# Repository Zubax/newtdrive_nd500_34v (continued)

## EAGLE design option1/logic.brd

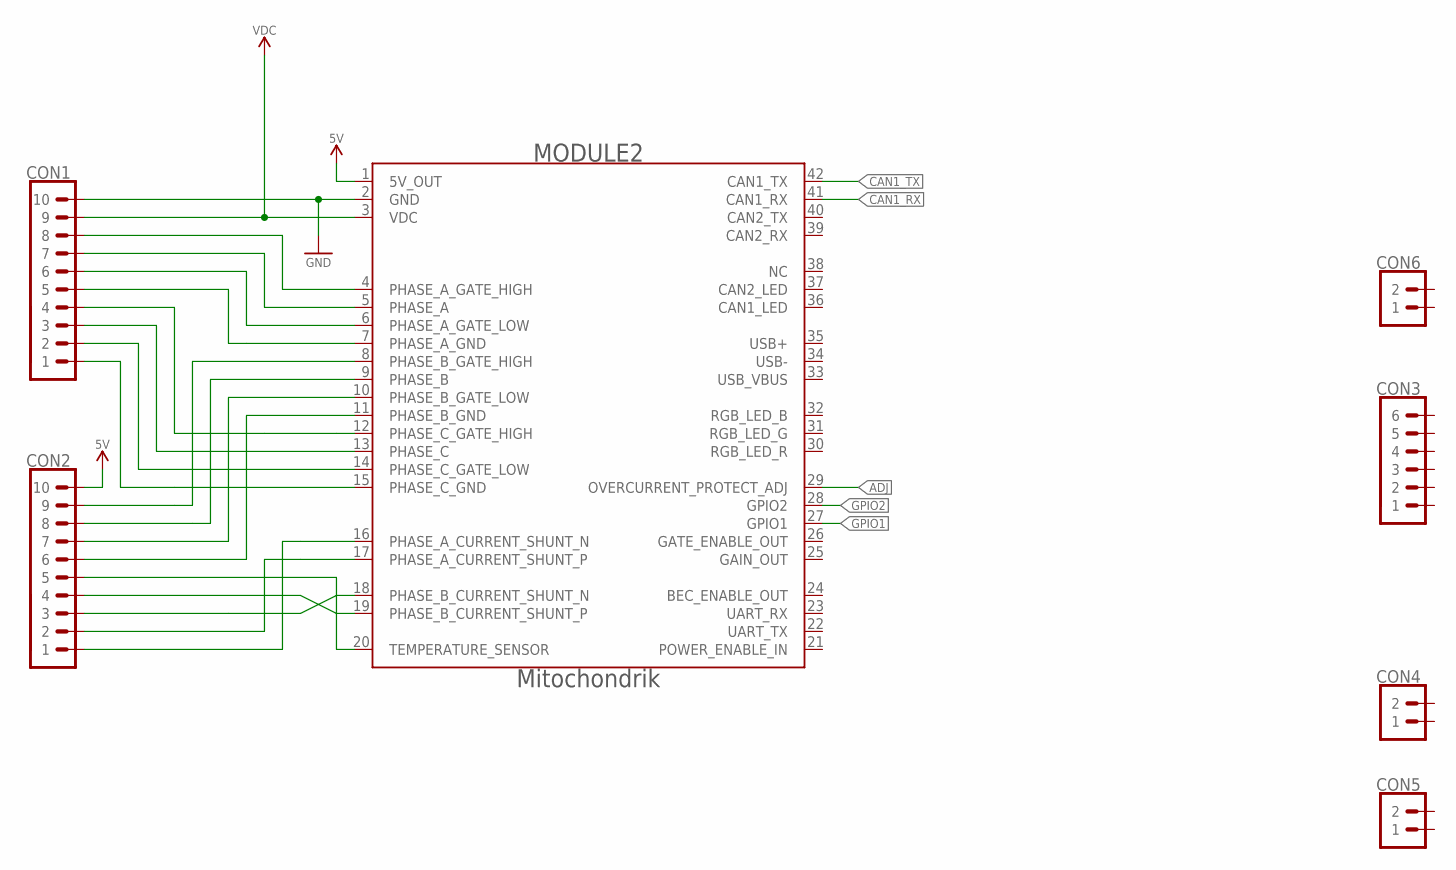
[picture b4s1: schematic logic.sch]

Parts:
CON1, CON2: PINHEAD_1X10-2; 1X10-PTH_2
CON3: PINHEAD_1X06-2; 1X06-PTH-2
CON4, CON5, CON6: PINHEAD_1X02-2; 1X02-PTH-2
MODULE2: MITOHONDRIQUE-TH; MITOHONDRIQUE

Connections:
ADJ: CON3.2, MODULE2.29 (OVERCURRENT_PROTECT_ADJ)
BLUE: CON3.1, MODULE2.32 (RGB_LED_B)
CAN1_LED: CON3.6, MODULE2.36 (CAN1_LED)
CAN1_RX: CON3.4, MODULE2.41 (CAN1_RX)
CAN1_TX: CON3.5, MODULE2.42 (CAN1_TX)
GND: CON1.10, CON5.2, CON6.2, MODULE2.2 (GND)
GPIO1: CON3.3, CON6.1, MODULE2.27 (GPIO1)
GPIO2: MODULE2.28 (GPIO2)
GREEN: CON4.2, MODULE2.31 (RGB_LED_G)
unnamed: CON2.3, MODULE2.18 (PHASE_B_CURRENT_SHUNT_N)
unnamed: CON2.2, MODULE2.17 (PHASE_A_CURRENT_SHUNT_P)
unnamed: CON2.1, MODULE2.16 (PHASE_A_CURRENT_SHUNT_N)
unnamed: CON2.4, MODULE2.19 (PHASE_B_CURRENT_SHUNT_P)
unnamed: CON1.1, MODULE2.15 (PHASE_C_GND)
PHASE_A: CON1.7, MODULE2.5 (PHASE_A)
PHASE_A_GATE_HIGH: CON1.8, MODULE2.4 (PHASE_A_GATE_HIGH)
PHASE_A_GATE_LOW: CON1.6, MODULE2.6 (PHASE_A_GATE_LOW)
PHASE_A_GND: CON1.5, MODULE2.7 (PHASE_A_GND)
PHASE_B: CON1.3, MODULE2.13 (PHASE_C)
PHASE_B_GATE_HIGH: CON1.4, MODULE2.12 (PHASE_C_GATE_HIGH)
PHASE_B_GATE_LOW: CON1.2, MODULE2.14 (PHASE_C_GATE_LOW)
PHASE_C: CON2.8, MODULE2.9 (PHASE_B)
PHASE_C_GATE_HIGH: CON2.9, MODULE2.8 (PHASE_B_GATE_HIGH)
PHASE_C_GATE_LOW: CON2.7, MODULE2.10 (PHASE_B_GATE_LOW)
PHASE_C_GND: CON2.6, MODULE2.11 (PHASE_B_GND)
RED: CON4.1, MODULE2.30 (RGB_LED_R)
TEMPERATURE_SENSOR: CON2.5, MODULE2.20 (TEMPERATURE_SENSOR)
VDC: CON1.9, MODULE2.3 (VDC)
VDD_5V: CON2.10, CON5.1, MODULE2.1 (5V_OUT)

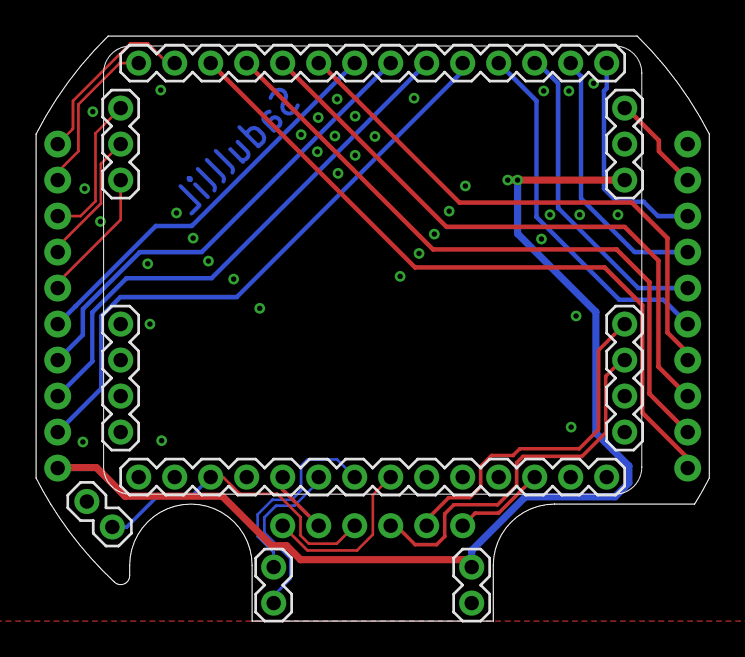
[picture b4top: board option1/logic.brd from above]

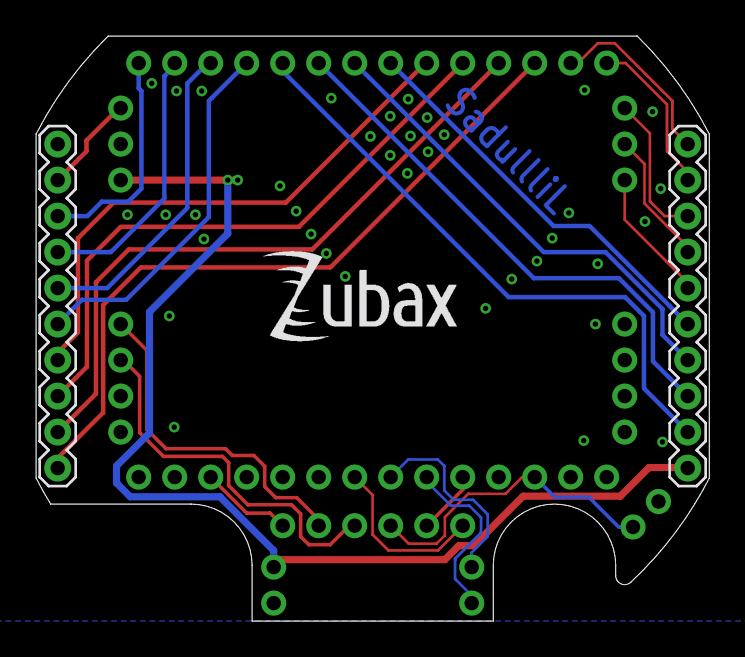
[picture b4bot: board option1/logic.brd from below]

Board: 2 copper layers, 37.4 x 32.5 mm, 8 parts (3 on the bottom side), 28 nets.

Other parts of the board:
U$1: ZUBAX_LOGO_5X10

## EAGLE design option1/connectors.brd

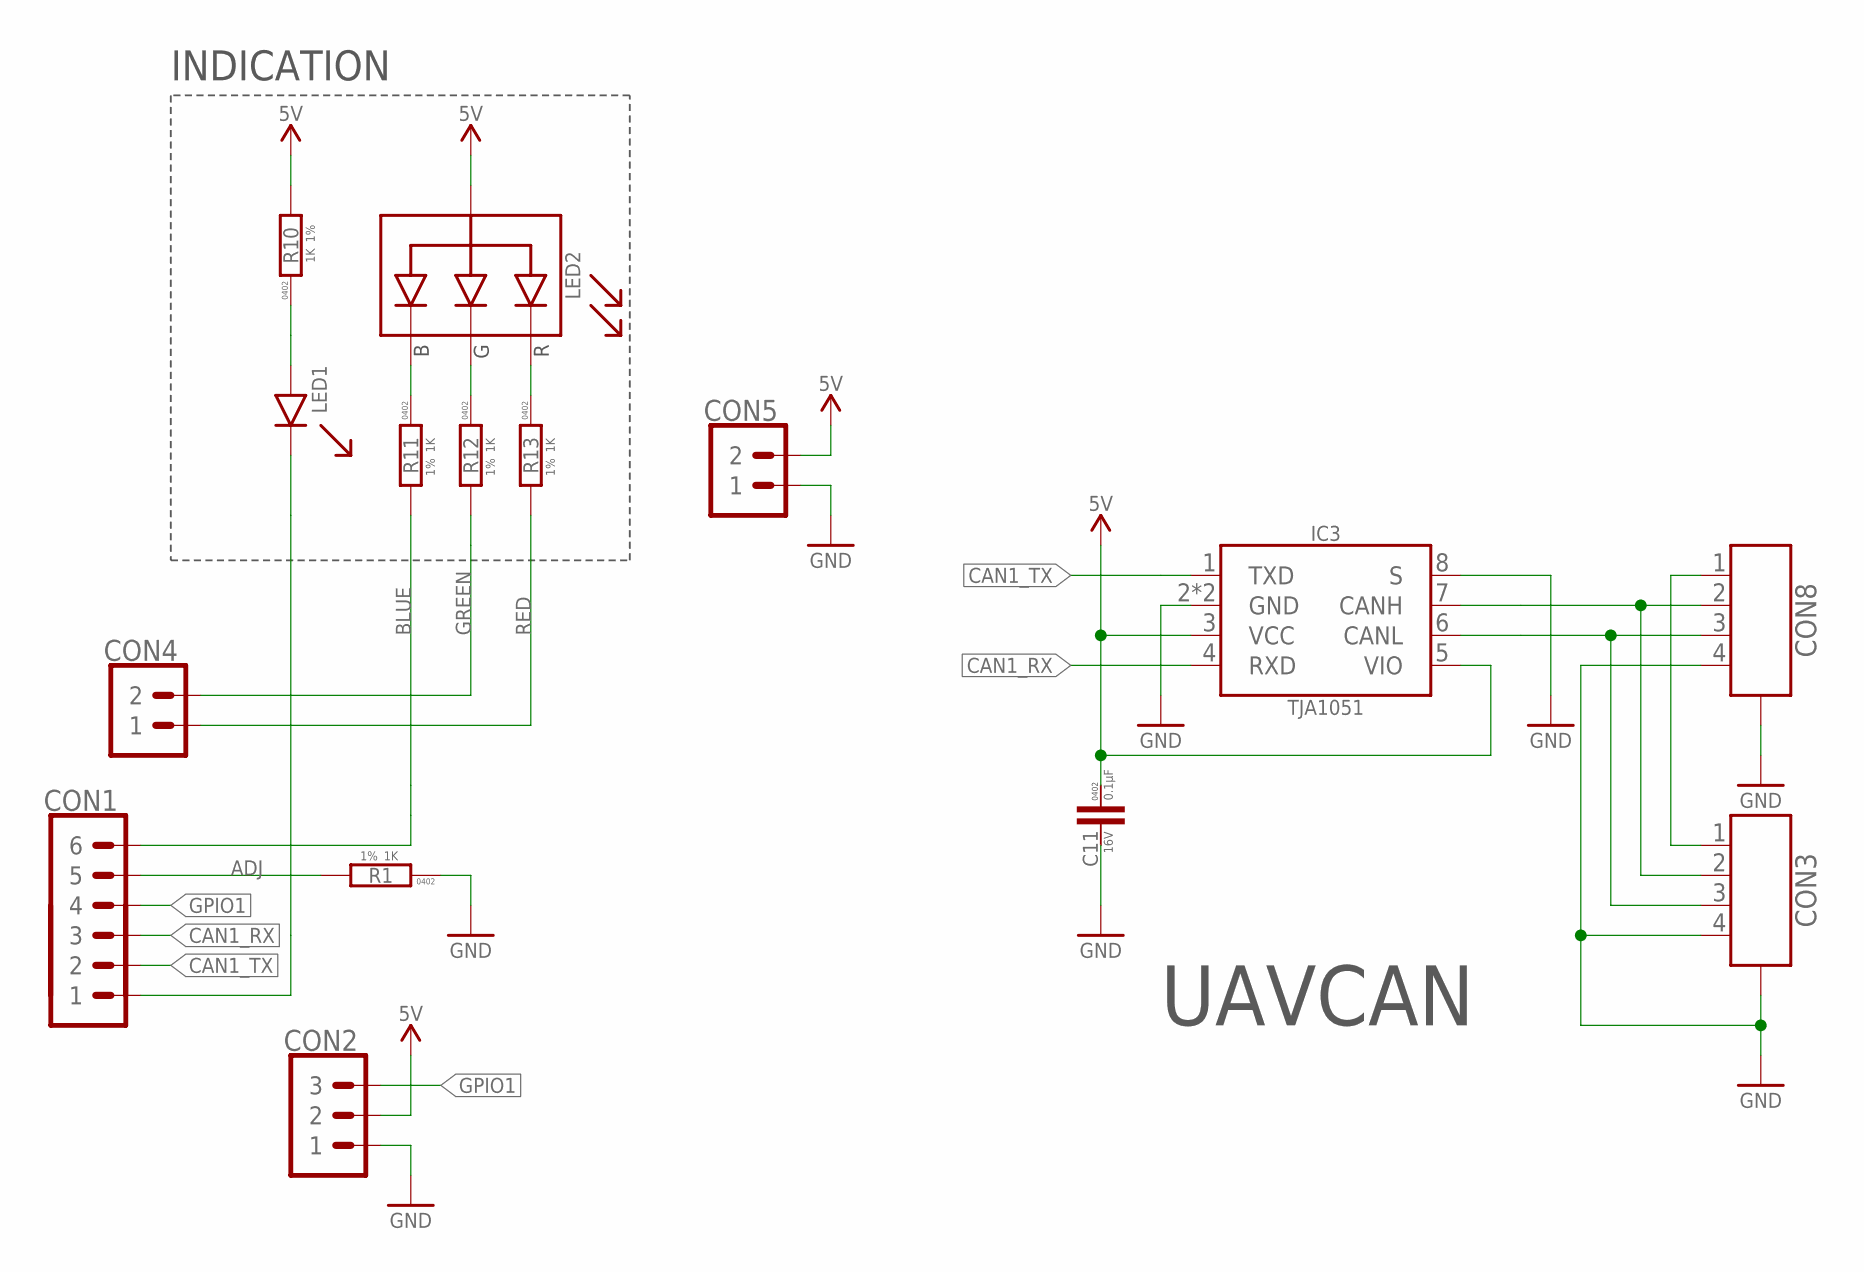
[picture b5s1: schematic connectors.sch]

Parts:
C11: 0.1µF; C0402
CON1: PINHEAD_1X06-2; 1X06-PTH-2
CON2: PINHEAD_1X03-2.54-RA; 1X03-PTH-2.54-RA
CON3, CON8: CON-4P-JST_GH-RA; JST_GH-4P-RA
CON4, CON5: PINHEAD_1X02-2; 1X02-PTH-2
IC3: TJA1051; SOT782-1
LED1: GREEN; 0402_LED
LED2: LTST-C19HE1WT; LITE_ON_RGB_LED
R1, R10, R11, R12, R13: 1K; R0402

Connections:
ADJ: CON1.5, R1.2
BLUE: CON1.6, R11.2
CAN1_LED: CON1.1, LED1.C
CAN1_RX: CON1.3, IC3.4 (RXD)
CAN1_TX: CON1.2, IC3.1 (TXD)
GND: C11.2, CON2.1, CON3.4, CON3.M$0 (GND), CON3.M$1 (GND), CON5.1, CON8.4, CON8.M$0 (GND), CON8.M$1 (GND), IC3.2 (GND), IC3.8 (S), IC3.PAD (GND), R1.1
GPIO1: CON1.4, CON2.3
GREEN: CON4.2, R12.2
unnamed: LED1.A, R10.1
unnamed: CON3.2, CON8.2, IC3.7 (CANH)
unnamed: CON3.1, CON8.1
unnamed: CON3.3, CON8.3, IC3.6 (CANL)
unnamed: LED2.R, R13.1
unnamed: LED2.G, R12.1
unnamed: LED2.B, R11.1
RED: CON4.1, R13.2
VDD_5V: C11.1, CON2.2, CON5.2, IC3.3 (VCC), IC3.5 (VIO), LED2.+ (A), R10.2

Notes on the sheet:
INDICATION
UAVCAN

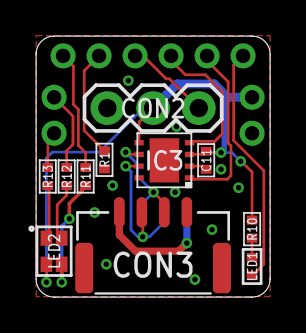
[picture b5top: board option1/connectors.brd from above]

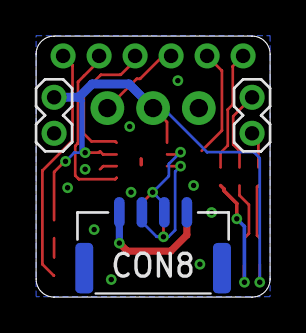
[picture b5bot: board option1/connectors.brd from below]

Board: 2 copper layers, 13.0 x 14.5 mm, 15 parts (4 on the bottom side), 17 nets.

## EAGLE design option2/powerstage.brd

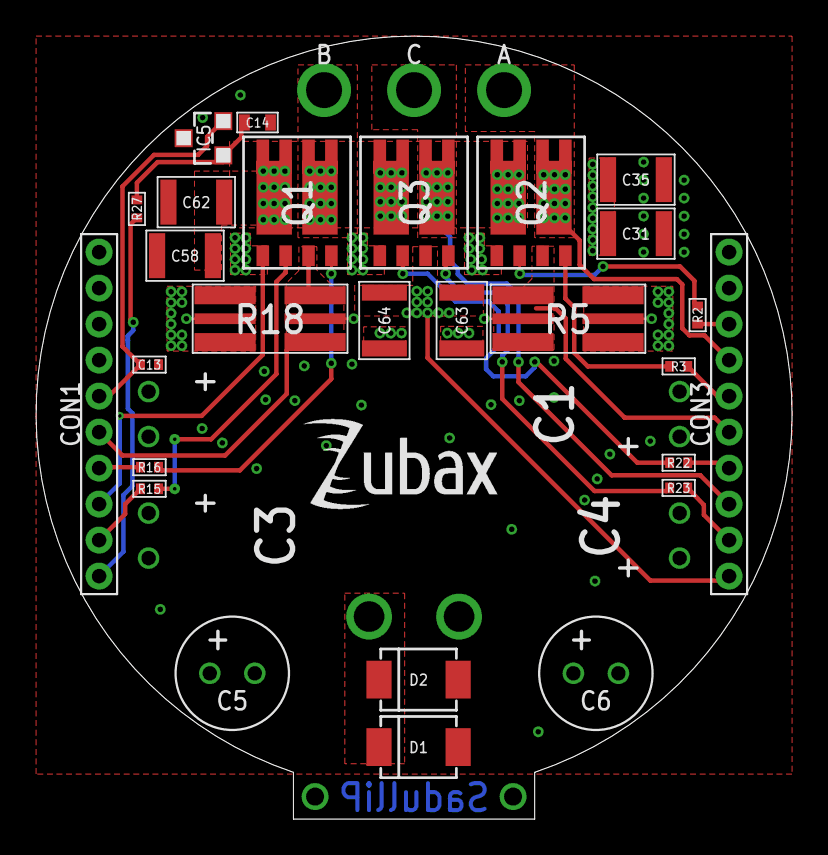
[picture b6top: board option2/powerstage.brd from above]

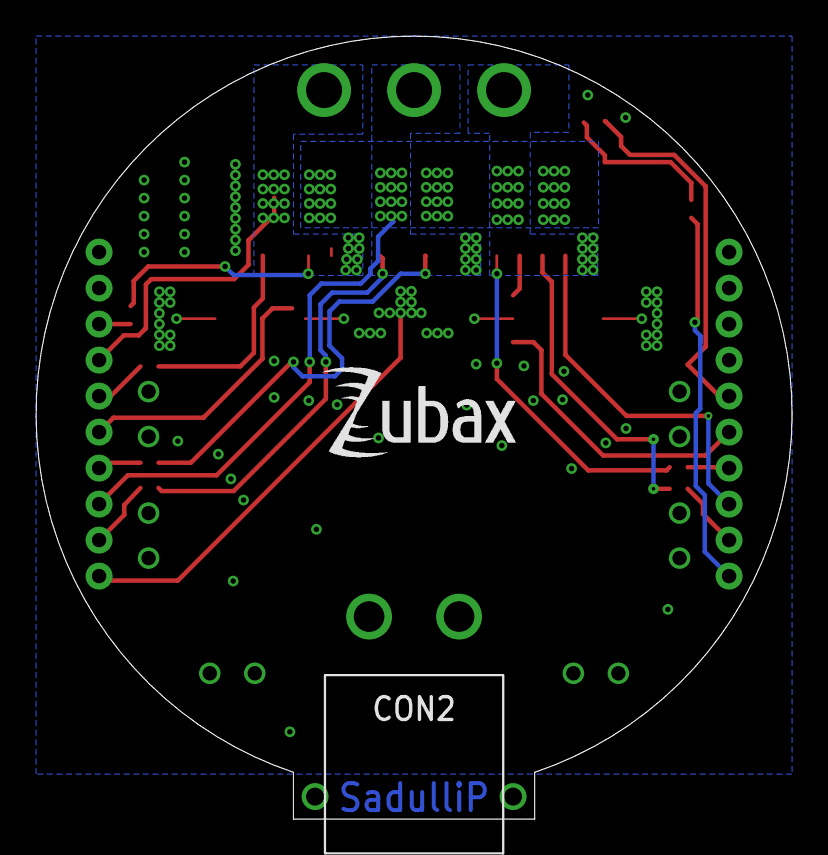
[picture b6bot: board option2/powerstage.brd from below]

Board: 4 copper layers, 42.0 x 43.5 mm, 38 parts (2 on the bottom side), 27 nets.

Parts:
A: PAD-HOLE_2; HOLE_2
B: PAD-HOLE_2; HOLE_2
C: PAD-HOLE_2; HOLE_2
C1, C2, C3, C4: RADIAL_6.3X12.5-RA
C5, C6: RADIAL_6.3X12.5
C13: 0.1µF; C0402
C14: 4.7µF; C0603
C31, C35, C58, C62, C63, C64: 4.7µF; C1210
CON1, CON3: PINHEAD_1X10-2-FEMALE; 1X10-PTH_2-FEMALE
CON2: BATTERY_CON-2P-XT30-RA; XT30-RA
D1, D2: PTVS36VP1UP,115-36V-SOD128; SOD128
IC5: MCP9700; SOT23B-3
Q1, Q2, Q3: BUK7K6R2-40EX; SOT-1205
R2, R3, R15, R16, R22, R23: 4R3; R0402
R5, R18: 1 mOhms; R2512-KELVIN
R27: 200R; R0402
S1: SENSE; SENSE-0.6
U$1, U$13: ZUBAX_LOGO_5X10

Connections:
unnamed: Q2.2, R2.2
unnamed: Q2.4, R3.2
unnamed: Q1.2, R15.2
unnamed: Q1.4, R16.2
unnamed: C14.P$2, IC5.1, R27.1
unnamed: Q3.2, R22.2
unnamed: Q3.4, R23.2
PGND: C1.-, C2.-, C3.-, C4.-, C5.-, C6.-, C13.1, C14.P$1, C31.1, C35.1, C58.1, C62.1, C63.1, C64.1, CON2.-, D1.A, D2.A, IC5.3, Q3.3, R5.2, R5.22, R18.2, R18.22, S1.SHELL
PHASE_A: A.P$1, CON3.7, Q2.1, Q2.5, Q2.6, Q2.EP-5-6
PHASE_A_CURRENT_SHUNT_N: CON1.8, R5.S1
PHASE_A_CURRENT_SHUNT_P: CON1.7, R5.S2
PHASE_A_GATE_HIGH: CON3.8, R2.1
PHASE_A_GATE_LOW: CON3.6, R3.1
PHASE_A_GND: CON3.5, Q2.3, R5.1, R5.11
PHASE_B: B.P$1, CON1.3, Q1.1, Q1.5, Q1.6, Q1.EP-5-6
PHASE_B_CURRENT_SHUNT_N: CON1.10, R18.S1
PHASE_B_CURRENT_SHUNT_P: CON1.9, R18.S2
PHASE_B_GATE_HIGH: CON1.2, R15.1
PHASE_B_GATE_LOW: CON1.4, R16.1
PHASE_B_GND: CON1.5, Q1.3, R18.1, R18.11
PHASE_C: C.P$1, CON3.3, Q3.1, Q3.5, Q3.6, Q3.EP-5-6
PHASE_C_GATE_HIGH: CON3.4, R22.1
PHASE_C_GATE_LOW: CON3.2, R23.1
PHASE_C_GND: CON3.1, S1.IN
TEMPERATURE_SENSOR: C13.2, CON1.6, IC5.2
VDC: C1.+, C2.+, C3.+, C4.+, C5.+, C6.+, C31.2, C35.2, C58.2, C62.2, C63.2, C64.2, CON2.+, CON3.9, D1.C, D2.C, Q1.7, Q1.8, Q1.EP-7-8, Q2.7, Q2.8, Q2.EP-7-8, Q3.7, Q3.8, Q3.EP-7-8
VDD_5V: CON1.1, R27.2

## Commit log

2018-11-08 initial import
2018-11-08 silk updates
2018-11-08 Options
2018-11-09 updates here and there
2018-11-09 Roting is completed
2018-11-09 routing finished
2018-11-09 pcb outline updated
2018-11-09 powerstage polygones fixes
2018-11-09 logic board outline fix
2018-11-09 powerstage updates
2018-11-09 BOM added
2018-11-09 DUCK is here
2018-11-10 OSHW logo
2018-11-10 here comes UAVCAN BEC output
2018-11-11 Routing is complete again. Now with BEC output
2018-11-11 proper powerstage outline
2018-11-11 bloody connectors had to be moved
2018-11-11 bloody connectors
2018-11-11 minor mask fixes
2018-11-11 inner layers update
2018-11-11 connectors pcb outline update
2018-11-11 connectors pcb fillets
2018-11-11 poly update
2018-11-12 cleanup
2018-11-12 pinout fixes
2018-11-12 proper CAM file added
2018-11-12 gerber files added
2018-11-12 powerstage 40V version BOM
2018-11-12 fiducial marks
2018-11-12 powerstage assembly files
2018-11-12 connectors PCB BOM
2018-11-12 more assembly drawings added
2018-11-12 logic PCB BOM
2018-11-12 naming
2018-11-26 Logic board update.
    Thermistor connection moved to other side of the PCB
2018-11-26 1210 ceramic capacitors replaced with better ones
2018-11-27 fixed logic board to fit housing better
2018-12-07 typo
2018-12-17 updated compnents naming. Updated production docs
2019-03-05 Create LICENSE
2019-03-27 PCB stack files added
2019-03-27 PCB stack updates
2019-03-27 UAVCAN logo
2019-03-28 link to the BOM spreadsheet
2019-03-29 let there be a giant hole in the middle of the PCB
2019-03-29 Library update
2019-03-29 let there be holes in powerstage as well
2019-03-29 Silkscreen fix
2019-03-29 Bloody fiducial marks
2019-03-29 damn duck logo
2019-03-30 offline BOM added
2019-03-30 3d model added
2019-04-06 TVS diode replaced
2019-04-10 motor characteristics
2019-04-10 Motor temperature measurement
2019-04-10 Mechanical characteristics
2019-04-10 Battery voltage changed
2019-04-10 grammatics and formatting
2019-04-10 draft mark
2019-04-11 mechanical drawings update
2019-04-11 urls and eps files addition
2019-04-11 propeller accessories
2019-04-18 there's no more references on sapog
2019-04-20 motor temperature error correct
2019-04-22 document templates remove
2019-04-22 doc templates moved to submodule
2019-04-23 more cleanup
2019-04-23 lines around sections and chapters.
2019-04-26 typos
2019-04-26 3d view import
2019-06-29 tools
2019-07-02 3d view added
2020-01-06 migration to the latest version of mitochondrik library
2020-02-24 pics for docs added
2020-02-26 Revert "pics for docs added"
    This reverts commit e4bd04d1e907848d9f90469a2b83f0fd6fc3d7f8.
2020-02-26 Revert "Update README.md"
    This reverts commit 0b30361ff2daf7b7f9abf058423ccafdc3206967.
2020-02-26 readme update
2020-03-09 whole doc split into separate chapters; formatting fixes
2020-03-12 Mechanical specs table fix
2020-03-16 Fixed the compiling issue
2020-03-17 thrust figures update
2020-03-26 Updates according to the requested changes
2020-03-30 compiling script added
2020-04-03 Motor selection consideration section added
2020-04-07 thrust figures updated
2020-04-10 Minor rearrange
2020-04-14 Renaming for compatibility reasons.
2020-05-04 assembly instructions inital import
2020-08-02 Critical fixes to the README
2020-08-02 Rewrite the intro
2021-01-05 Apply final corrections to the assembly documentation
2021-01-05 Rename pics into figures; fix #9
2021-01-05 Add an assembly note to fix #6
2021-01-05 Assembly instructions (#8)
2021-01-05 Update the README to indicate the first stable release
2021-01-06 Update the README to indicate the first stable release (#10)
2023-01-03 Key added
2023-01-04 Key added (#14)
2023-04-27 updated assembly
    closes #15
    - updated assembly guide
    - replaced motor
    - replaced thermistor specification
    - updated Sadulli version
    - updated Sadulli readme
2023-04-27 updated table
2023-05-02 requested changes
    - replaced UAVCAN with Cyphal & added link to telega.zubax.com
    - removed all generated files
    need help with changing R1 to 27k & need to find new part number
2023-05-06 Change R1 to 27K
2023-05-08 Change R1 to 27K (#17)
2023-05-08 Remove the mention of the hardware over-current protection resistor from the README
2023-05-08 Alakdan & assembly (#16)
    * updated assembly
    closes #15
    - updated assembly guide
    - replaced motor
    - replaced thermistor specification
    - updated Sadulli version
2023-05-08 Add the Telega configuration section
2023-05-09 images
2023-05-09 cropped empty space
2023-05-09 Add the Telega configuration section (#18)
    * Add the Telega configuration section
    * Update README.md
    * images
    * cropped empty space
    * Update README.md
    ---------
2023-05-10 README: add aux.pull config
2023-05-15 updated attributes
    added MANF and MANF# attributes to the connectors and powerstage schematics
2023-05-15 updated attributes (#19)
    added MANF and MANF# attributes to the connectors and powerstage schematics
2023-11-03 set reference points for assembling MOSFETs and LED
2023-11-03 set reference points for assembling MOSFETs and LED (#21)
2024-04-24 Update README.md (#22)
2024-04-24 Update README.md
    added maximum continuous phase current amplitude 40 A
2024-04-24 Update README.md (#23)
    added maximum continuous phase current amplitude 40 A
